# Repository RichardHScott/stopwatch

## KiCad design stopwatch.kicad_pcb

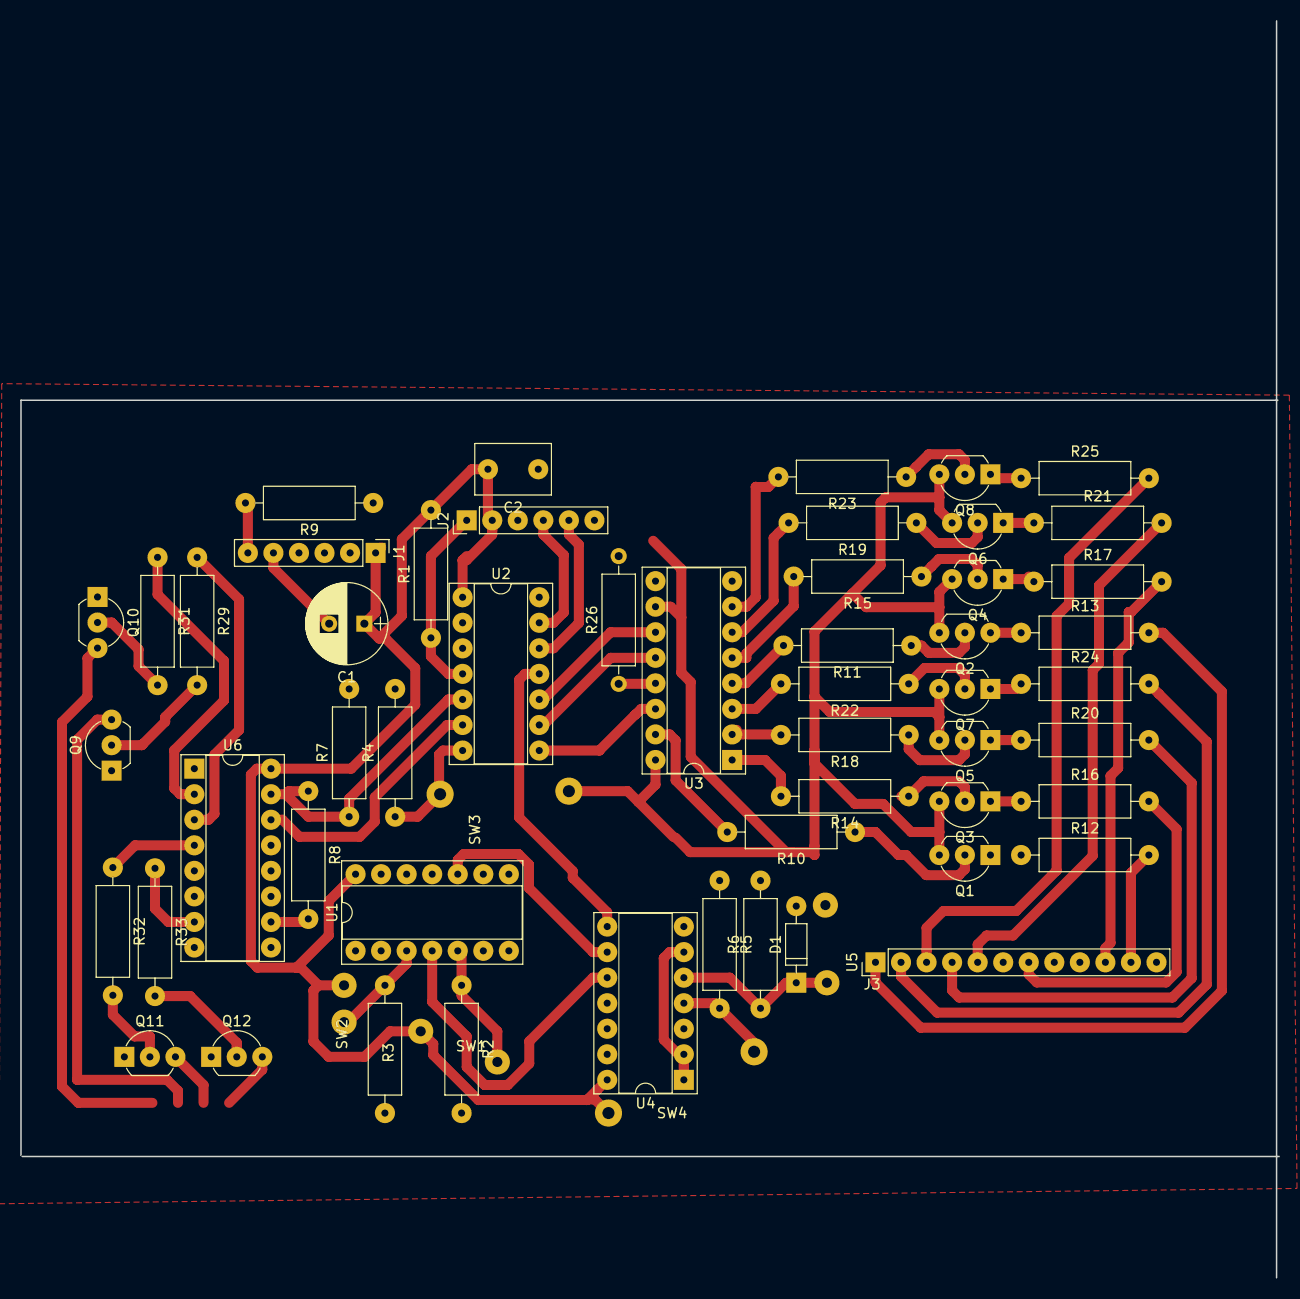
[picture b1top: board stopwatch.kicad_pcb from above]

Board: 2 copper layers, 125.1 x 125.0 mm, 58 parts (0 on the bottom side), 67 nets.

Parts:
C1: 47uF; CP_Radial_D8.0mm_P3.50mm
C2: 100nF; C_Disc_D7.5mm_W5.0mm_P5.00mm
D1: D_Zener; D_DO-35_SOD27_P7.62mm_Horizontal
J1: USB_B_Micro; Pin_Header_Straight_1x06_Pitch2.54mm
J2: Conn_01x06; Pin_Header_Straight_1x06_Pitch2.54mm
J3: Conn_Coaxial; WireConnection_1.00mmDrill
Q1, Q2, Q3, Q4, Q5, Q6, Q7, Q8, Q9, Q10, Q11, Q12: 2N3904; TO-92_Inline_Wide
R1: 5k; R_Axial_DIN0309_L9.0mm_D3.2mm_P12.70mm_Horizontal
R2, R3, R4, R5, R6, R7: 100k; R_Axial_DIN0309_L9.0mm_D3.2mm_P12.70mm_Horizontal
R8, R10, R11, R14, R15, R18, R19, R22, R23, R26: 10k; R_Axial_DIN0309_L9.0mm_D3.2mm_P12.70mm_Horizontal
R9: 1M; R_Axial_DIN0309_L9.0mm_D3.2mm_P12.70mm_Horizontal
R12, R13, R16, R17, R20, R21, R24, R25: 500; R_Axial_DIN0309_L9.0mm_D3.2mm_P12.70mm_Horizontal
R29, R31, R32, R33: 200; R_Axial_DIN0309_L9.0mm_D3.2mm_P12.70mm_Horizontal
SW1, SW2: SW_Push; WireConnection_1.00mmDrill
SW3, SW4: SW_SPST; WireConnection_1.20mmDrill
U1: 74HC14; DIP-14_W7.62mm_Socket
U2: PIC16F616-IP; DIP-14_W7.62mm_Socket
U3: 74HC595; DIP-16_W7.62mm_Socket
U4: 74HC00; DIP-14_W7.62mm_Socket
U5: CA56-12CGKWA; Pin_Header_Straight_1x12_Pitch2.54mm
U6: 4017; DIP-16_W7.62mm_Socket

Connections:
+5V: C1.1, C2.2, J1.1, J2.2, Q1.3, Q2.3, Q3.3, Q4.3, Q5.3, Q6.3, Q7.3, Q8.3, R1.2, SW1.1, SW2.1, SW3.1, SW4.1, U1.14, U2.1, U3.10, U3.16, U4.14, U6.16
/CA1: R29.1, U6.3
/CA2: R31.1, U6.2
/CA3: R32.1, U6.4
/CA4: R33.1, U6.7
/CONTINUE: R4.1, SW3.2, U2.7
/CTR_CLK: U2.6, U6.14
/EXT_TRIGGER: U1.11, U4.3
/ICSPCLK: J2.5, U2.12
/ICSPDAT: J2.4, U2.13
/MANUAL_TRIGGER: U1.4, U4.10
/MCLR: J2.1, R1.1, U2.4
/QA: R10.2, U3.15
/QB: R14.2, U3.1
/QC: R18.2, U3.2
/QD: R22.2, U3.3
/QDP: R23.2, U3.7
/QE: R11.2, U3.4
/QF: R15.2, U3.5
/QG: R19.2, U3.6
/RESET_CTR: R7.1, R8.1, U2.5, U6.15
/TRIGGER: U2.11, U4.8
/WATCH_CLK: U2.10, U3.11
/WATCH_DATA: U2.8, U3.14
/WATCH_RCLK: U2.9, U3.12
/a: R12.2, U5.11
/b: R16.2, U5.7
/c: R20.2, U5.4
/d: R24.2, U5.2
/dp: R25.2, U5.3
/e: R13.2, U5.1
/f: R17.2, U5.10
/g: R21.2, U5.5
GND: C1.2, C2.1, D1.2, J1.5, J2.3, J3.2, Q9.1, Q10.1, Q11.1, Q12.1, R2.2, R3.2, R4.2, R5.1, R6.2, R7.2, R9.1, R26.2, U1.7, U2.14, U3.8, U4.7, U6.8, U6.13
unnamed: D1.1, J3.1, R6.1, U4.5
unnamed: J1.6, R9.2
unnamed: Q1.1, R12.1
unnamed: Q1.2, R10.1
unnamed: Q2.1, R13.1
unnamed: Q2.2, R11.1
unnamed: Q3.1, R16.1
unnamed: Q3.2, R14.1
unnamed: Q4.1, R17.1
unnamed: Q4.2, R15.1
unnamed: Q5.1, R20.1
unnamed: Q5.2, R18.1
unnamed: Q6.1, R21.1
unnamed: Q6.2, R19.1
unnamed: Q7.1, R24.1
unnamed: Q7.2, R22.1
unnamed: Q8.1, R25.1
unnamed: Q8.2, R23.1
unnamed: Q9.2, R29.2
unnamed: Q9.3, U5.12
unnamed: Q10.2, R31.2
unnamed: Q10.3, U5.9
unnamed: Q11.2, R32.2
unnamed: Q11.3, U5.8
unnamed: Q12.2, R33.2
unnamed: Q12.3, U5.6
unnamed: R2.1, SW1.2, U1.5
unnamed: R3.1, SW2.2, U1.3
unnamed: R5.2, SW4.2, U4.4
unnamed: R8.2, U6.10
unnamed: R26.1, U3.13
unnamed: U1.10, U4.9
unnamed: U4.1, U4.2, U4.6

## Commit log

2018-08-15 Deboucing, extra switches.
2018-08-15 Add makefile
2018-08-15 Add kicad
